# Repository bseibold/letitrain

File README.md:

# Let it rain

An ESP32 board intended for use with TL-136 level sensors

## Status

Version 1 was built and is running well.

## Description

The sensor officially requires 24V, but in practice it runs well down to about 7V.
An op-amp is used to limit the current through the sensor and protect the ADC in case
of a short-circuit. The bias current of the op-amp has a small but measureable effect,
however the voltage measured by the ADC is still very linear to the current through the
sensor.

## Software

The board can be used with ESPHome, see [esphome.yaml](esphome.yaml) for an example configuration.

## BOM

 - 1x TL-136 differential pressure level sensor
 - 1x ESP32-WROOM-32x, can be any variant with the same footprint
 - 1x MCP3421 ADC converter
 - 1x OP07 Operational Amplifier
 - 1x MCP9700B temperature sensor (optional)
 - 1x DC-DC module with 780x compatible pins and 3.3V output. Must support 12-18V input

 - MLCC capacitors 0603, X5R or X7R, at least 6.3V
   - 5x 100nF (C1, C2, C3, C5, C6)
   - 1x 1µF (C2)
   - 2x 10µF (C4, C9)
 - MLCC capacitors 0603, X5R or X7R, at least 25V (better 50V)
   - 1x 100nF (C7)
   - 1x 1µF (C8)
 - 1x Polymer capacitor 5.0mm, at least 6.3V, 22µF (C10)
 - 1x Polymer capacitor 6.3mm, at least 25V (better 50V), 10µF (C11)
 - 1x Bidirectional TSV diode, SMA, voltage slightly above max. supply voltage (D1, optional)
 - 1x Pin header 0,1" 1x3 Pins (J3)
 - 1x BSS84 P-Channel Enhancement MOSFET (Q1)
 - 8x Resistor 0603, 10kOhm (R1, R3, R4, R9, R10, R11, R12, R15)
 - 2x Resistor 0603, 47kOhm (R2, R13)
 - 3x Resistor 0603, 1kOhm (R5, R6, R7)
 - 1x Resistor 0805, 100Ohm, high precision (R8)
 - 1x Resistor 0805, 33Ohm (R14)

Optional pin headers are omitted. They are intended for later reuse of spare PCBs.

The enclosure is an RL6115 from Hammond Manufacturing.

## Changelog

### Version 1.1

- Made more room for DC-DC module, it was a tight fit next to the capacitors
- Rotated TSV diode so that silkscreen is correct for unidirectional diodes
- Changed temperature sensor from MCP9701 to MCP9700B, changed footprint from SC70-5 to SOT23-3
- Some cosmetic fixes
- Marked optional stuff as DNP

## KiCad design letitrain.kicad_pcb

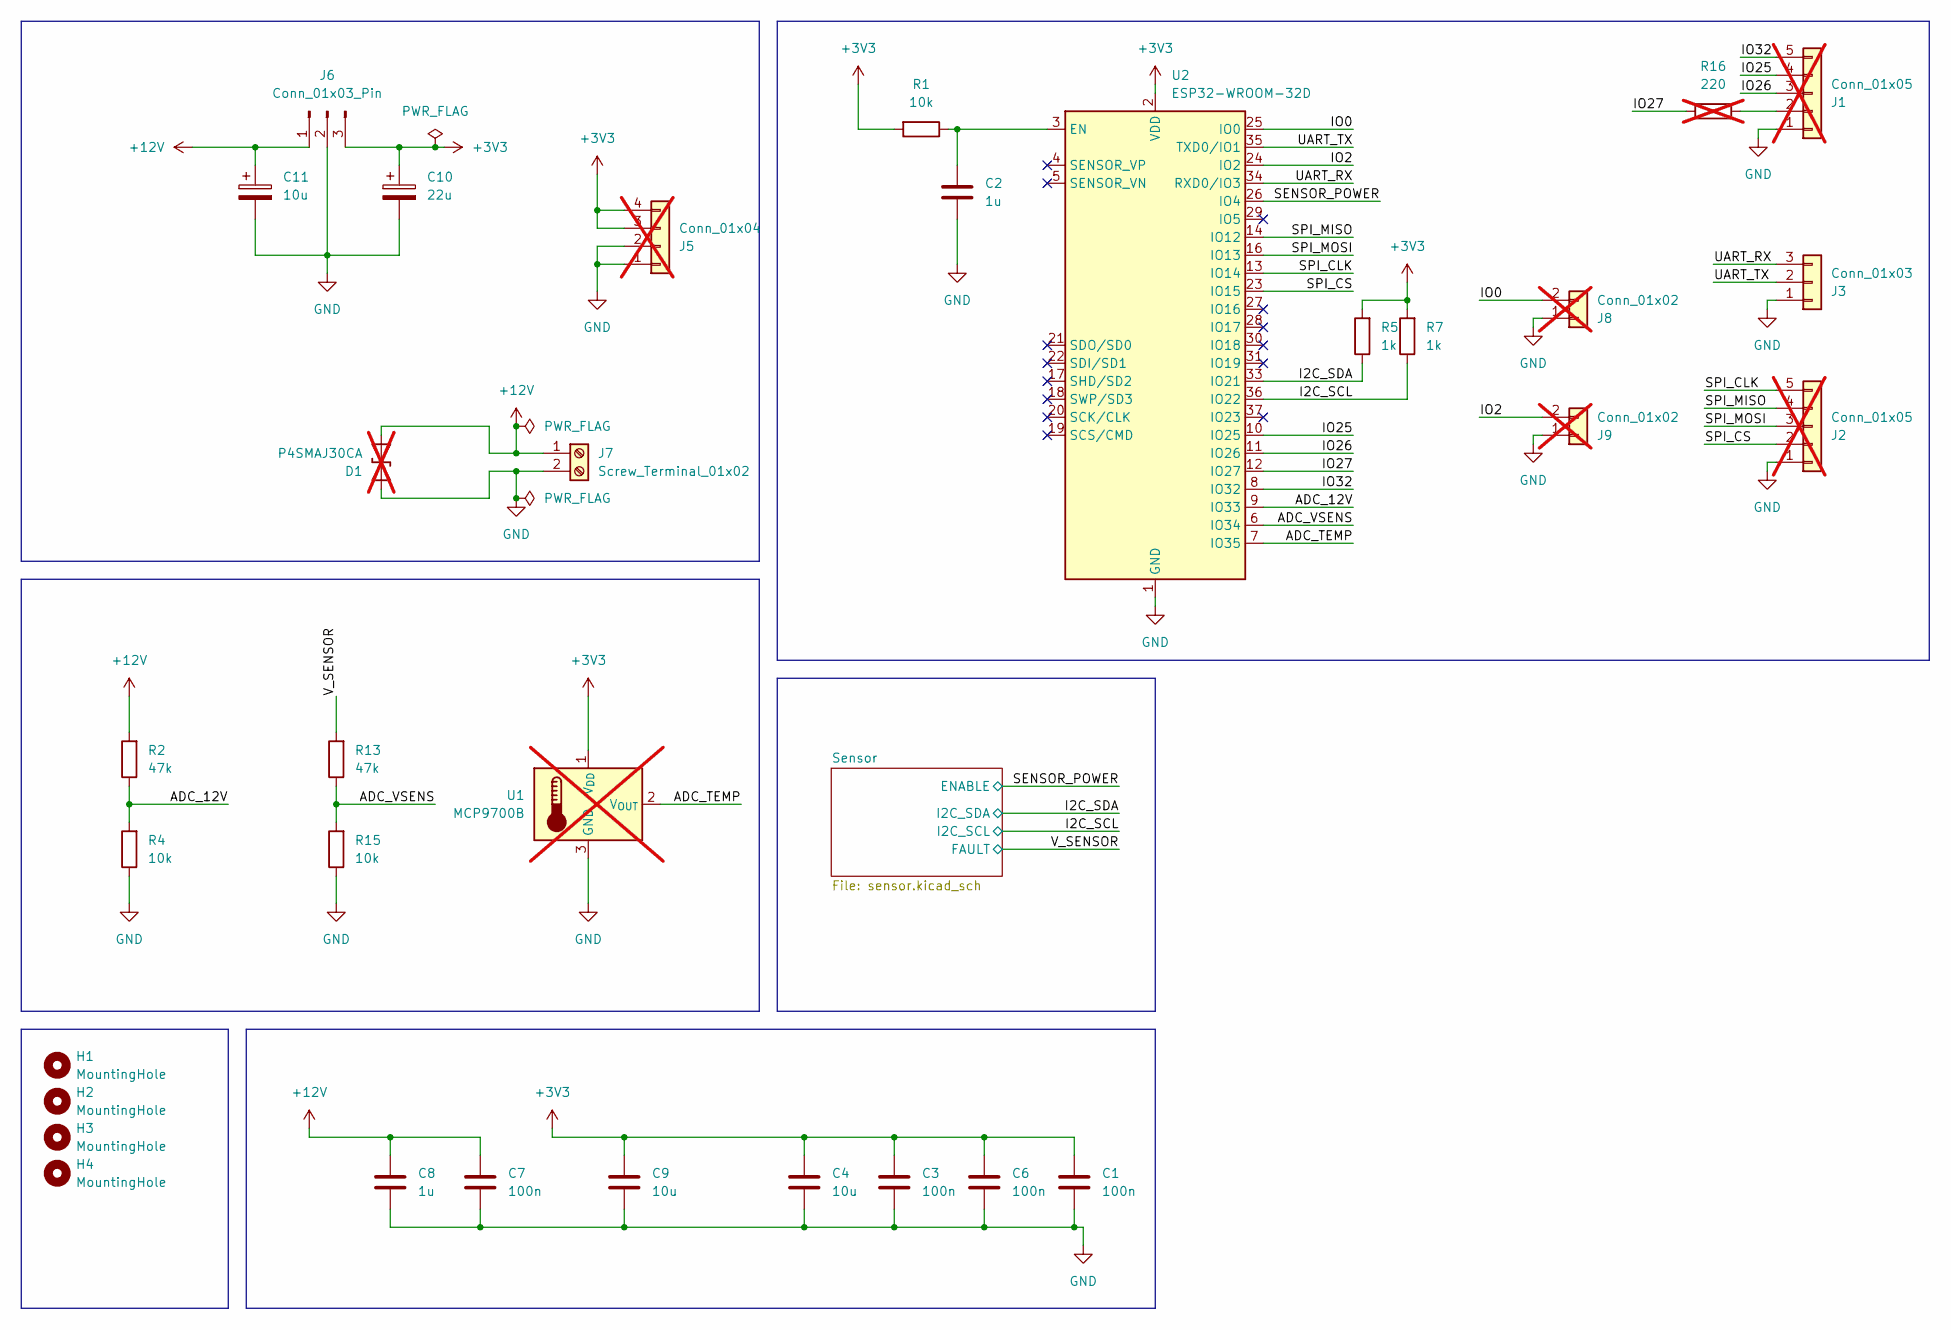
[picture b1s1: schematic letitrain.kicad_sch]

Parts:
C1, C3, C6, C7: 100n; C_0603_1608Metric_Pad1.08x0.95mm_HandSolder
C2, C8: 1u; C_0805_2012Metric_Pad1.18x1.45mm_HandSolder
C4, C9: 10u; C_0805_2012Metric_Pad1.18x1.45mm_HandSolder
C10: 22u; CP_Elec_5x5.8
C11: 10u; CP_Elec_6.3x5.8
D1: P4SMAJ30CA; D_SMA_Handsoldering; not fitted
H1, H2, H3, H4: MountingHole; MountingHole_3.2mm_M3
J1, J2: Conn_01x05; PinHeader_1x05_P2.54mm_Vertical; not fitted
J3: Conn_01x03; PinHeader_1x03_P2.54mm_Vertical
J5: Conn_01x04; PinHeader_1x04_P2.54mm_Vertical; not fitted
J6: Conn_01x03_Pin; PinHeader_1x03_P2.54mm_Vertical
J7: Screw_Terminal_01x02; TerminalBlock_MetzConnect_Type073_RT02602HBLU_1x02_P5.08mm_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
J8, J9: Conn_01x02; PinHeader_1x02_P2.54mm_Vertical; not fitted
R1, R4, R15: 10k; R_0603_1608Metric_Pad0.98x0.95mm_HandSolder
R2, R13: 47k; R_0603_1608Metric_Pad0.98x0.95mm_HandSolder
R5, R7: 1k; R_0603_1608Metric_Pad0.98x0.95mm_HandSolder
R16: 220; R_0603_1608Metric_Pad0.98x0.95mm_HandSolder; not fitted
U1: MCP9700B; SOT-23_Handsoldering; not fitted
U2: ESP32-WROOM-32D

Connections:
+3V3: C1.1, C3.1, C4.1, C6.1, C9.1, C10.1, J5.3, J5.4, J6.3, R1.2, R5.2, R7.2, U1.1 (V_{DD}), U2.2 (VDD); also elsewhere on the board
+12V: C7.1, C8.1, C11.1, D1.1 (A1), J6.1, J7.1, R2.2; also elsewhere on the board
/ADC_12V: R2.1, R4.2, U2.9 (IO33)
/ADC_TEMP: U1.2 (V_{OUT}), U2.7 (IO35)
/ADC_VSENS: R13.1, R15.2, U2.6 (IO34)
/I2C_SCL: R7.1, U2.36 (IO22); also elsewhere on the board
/I2C_SDA: R5.1, U2.33 (IO21); also elsewhere on the board
/IO0: J8.2, U2.25 (IO0)
/IO2: J9.2, U2.24 (IO2)
/IO25: J1.4, U2.10 (IO25)
/IO26: J1.3, U2.11 (IO26)
/IO27: R16.2, U2.12 (IO27)
/IO32: J1.5, U2.8 (IO32)
/SENSOR_POWER: U2.26 (IO4); also elsewhere on the board
/SPI_CLK: J2.5, U2.13 (IO14)
/SPI_CS: J2.2, U2.23 (IO15)
/SPI_MISO: J2.4, U2.14 (IO12)
/SPI_MOSI: J2.3, U2.16 (IO13)
/UART_RX: J3.3, U2.34 (RXD0/IO3)
/UART_TX: J3.2, U2.35 (TXD0/IO1)
/V_SENSOR: R13.2; also elsewhere on the board
GND: C1.2, C2.2, C3.2, C4.2, C6.2, C7.2, C8.2, C9.2, C10.2, C11.2, D1.2 (A2), J1.1, J2.1, J3.1, J5.1, J5.2, J6.2, J7.2, J8.1, J9.1, R4.1, R15.1, U1.3 (GND), U2.1 (GND), U2.15 (GND), U2.38 (GND), U2.39 (GND); also elsewhere on the board
unnamed: J1.2, R16.1
unnamed: C2.1, R1.1, U2.3 (EN)

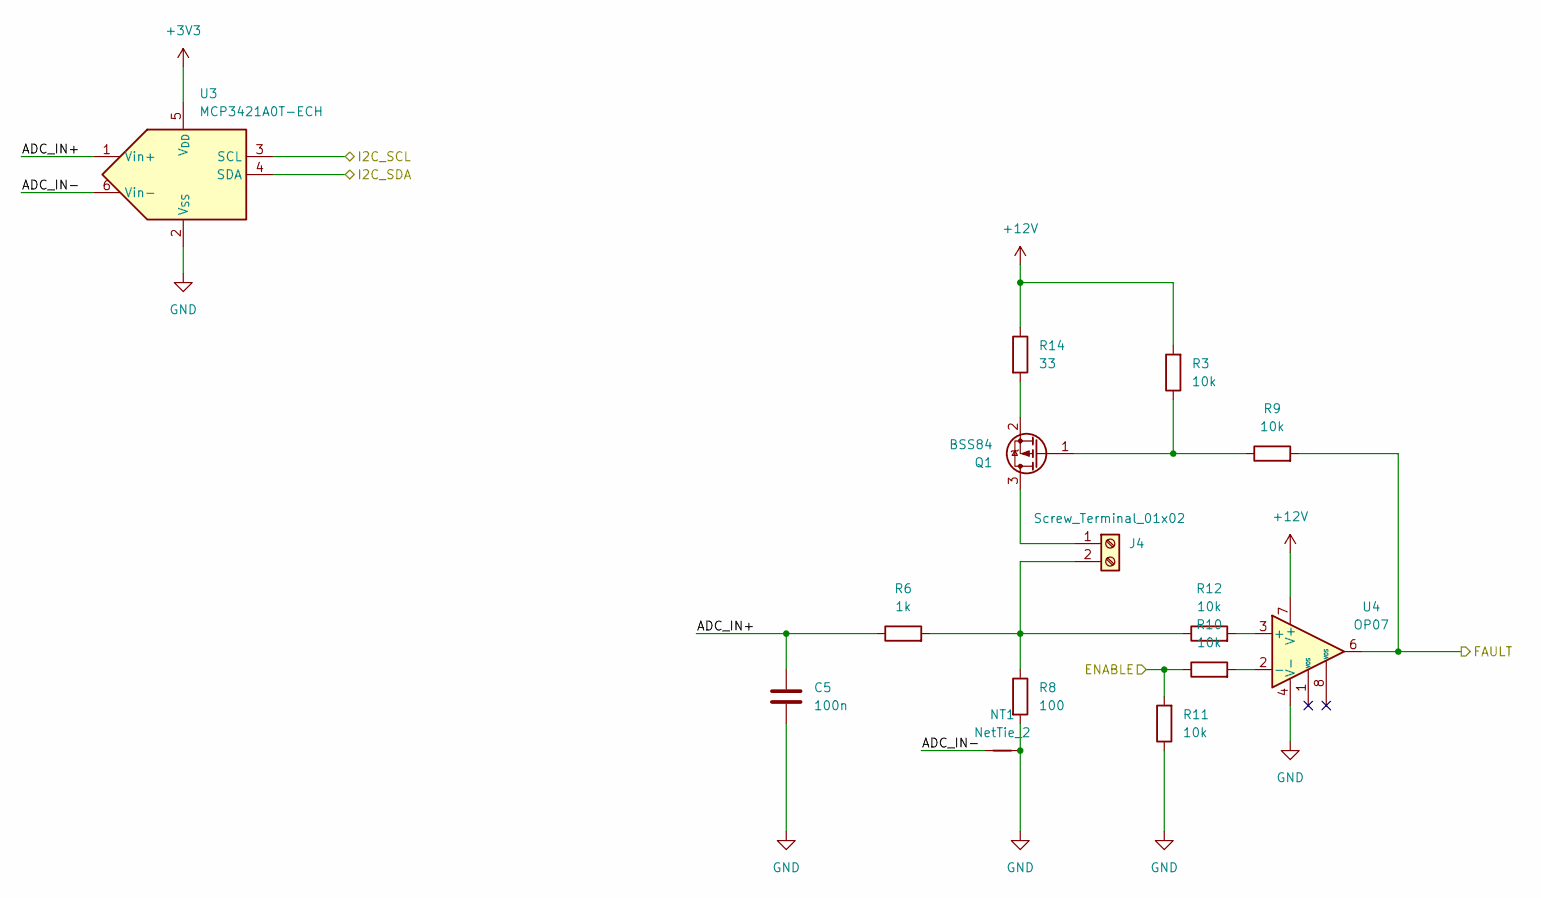
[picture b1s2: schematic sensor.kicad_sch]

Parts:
C5: 100n; C_0603_1608Metric_Pad1.08x0.95mm_HandSolder
J4: Screw_Terminal_01x02; TerminalBlock_MetzConnect_Type073_RT02602HBLU_1x02_P5.08mm_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
NT1: NetTie_2; NetTie-2_SMD_Pad0.5mm
Q1: BSS84; SOT-23
R3, R9, R10, R11, R12: 10k; R_0603_1608Metric_Pad0.98x0.95mm_HandSolder
R6: 1k; R_0603_1608Metric_Pad0.98x0.95mm_HandSolder
R8: 100; R_0805_2012Metric_Pad1.20x1.40mm_HandSolder
R14: 33; R_0805_2012Metric_Pad1.20x1.40mm_HandSolder
U3: MCP3421A0T-ECH; SOT-23-6
U4: OP07; SO-8_3.9x4.9mm_P1.27mm

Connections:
+3V3: U3.5 (V_{DD}); also elsewhere on the board
+12V: R3.2, R14.1, U4.7 (V+); also elsewhere on the board
/I2C_SCL: U3.3 (SCL); also elsewhere on the board
/I2C_SDA: U3.4 (SDA); also elsewhere on the board
/SENSOR_POWER: R10.1, R11.2; also elsewhere on the board
/Sensor/ADC_IN+: C5.2, R6.1, U3.1 (Vin+)
/Sensor/ADC_IN-: NT1.1, U3.6 (Vin-)
/V_SENSOR: R9.2, U4.6; also elsewhere on the board
GND: C5.1, NT1.2, R8.2, R11.1, U3.2 (V_{SS}), U4.4 (V-); also elsewhere on the board
unnamed: J4.1, Q1.3 (D)
unnamed: J4.2, R6.2, R8.1, R12.1
unnamed: Q1.1 (G), R3.1, R9.1
unnamed: Q1.2 (S), R14.2
unnamed: R12.2, U4.3 (+)
unnamed: R10.2, U4.2 (-)

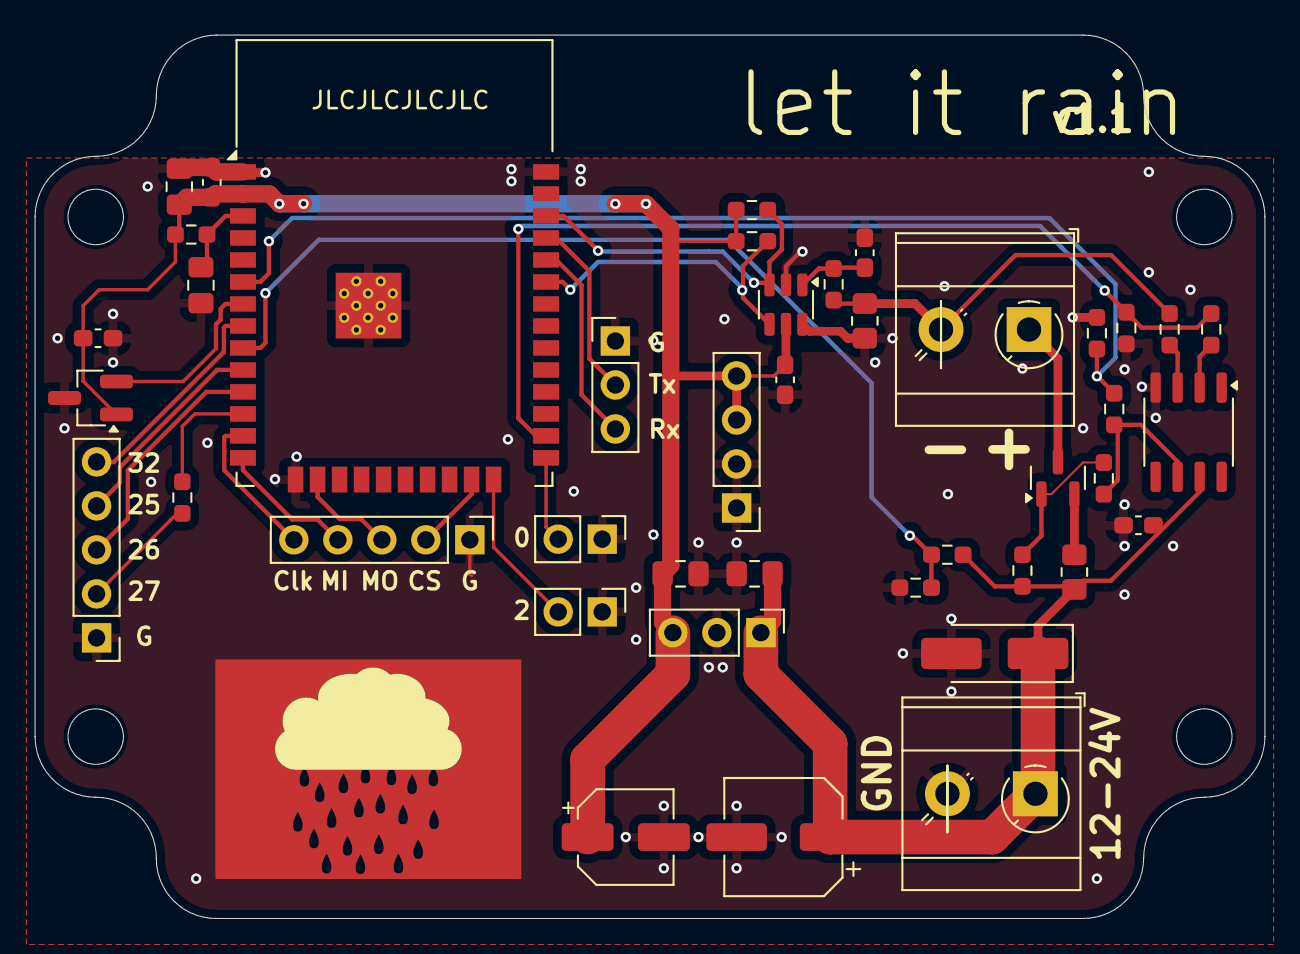
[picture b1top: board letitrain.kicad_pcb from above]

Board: 2 copper layers, 71.0 x 51.0 mm, 47 parts (0 on the bottom side), 32 nets.

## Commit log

2024-08-31 Add v1
2024-09-13 Add readme and license
2024-09-13 Add ESPHome config
2024-09-13 Add enclosure

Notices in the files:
letitrain.kicad_pcb:
© 2024 Bernhard Seibold
